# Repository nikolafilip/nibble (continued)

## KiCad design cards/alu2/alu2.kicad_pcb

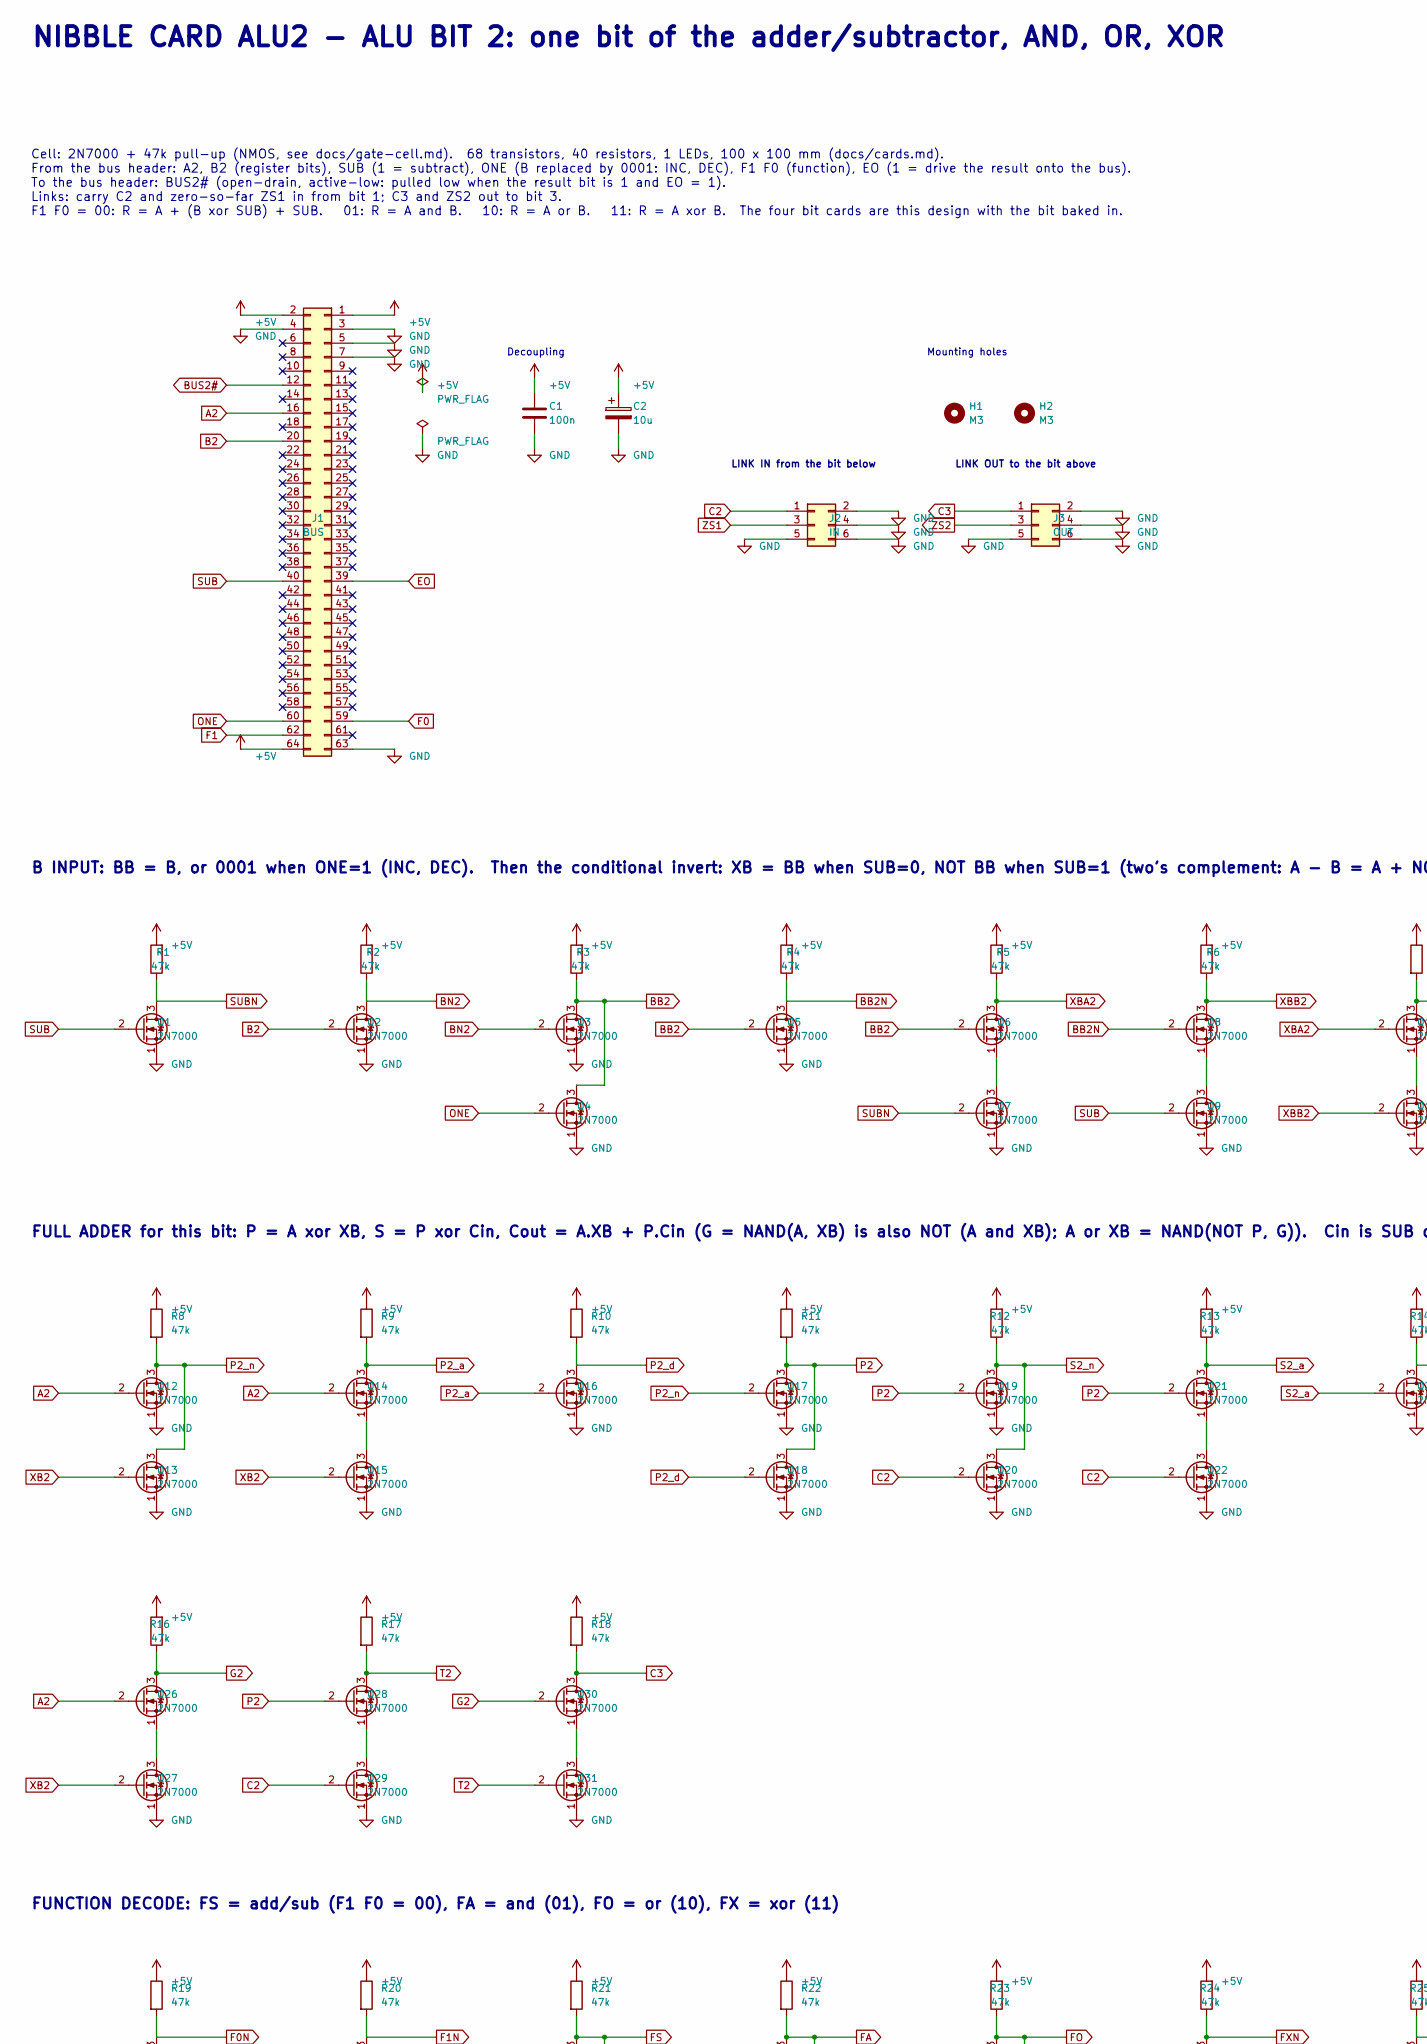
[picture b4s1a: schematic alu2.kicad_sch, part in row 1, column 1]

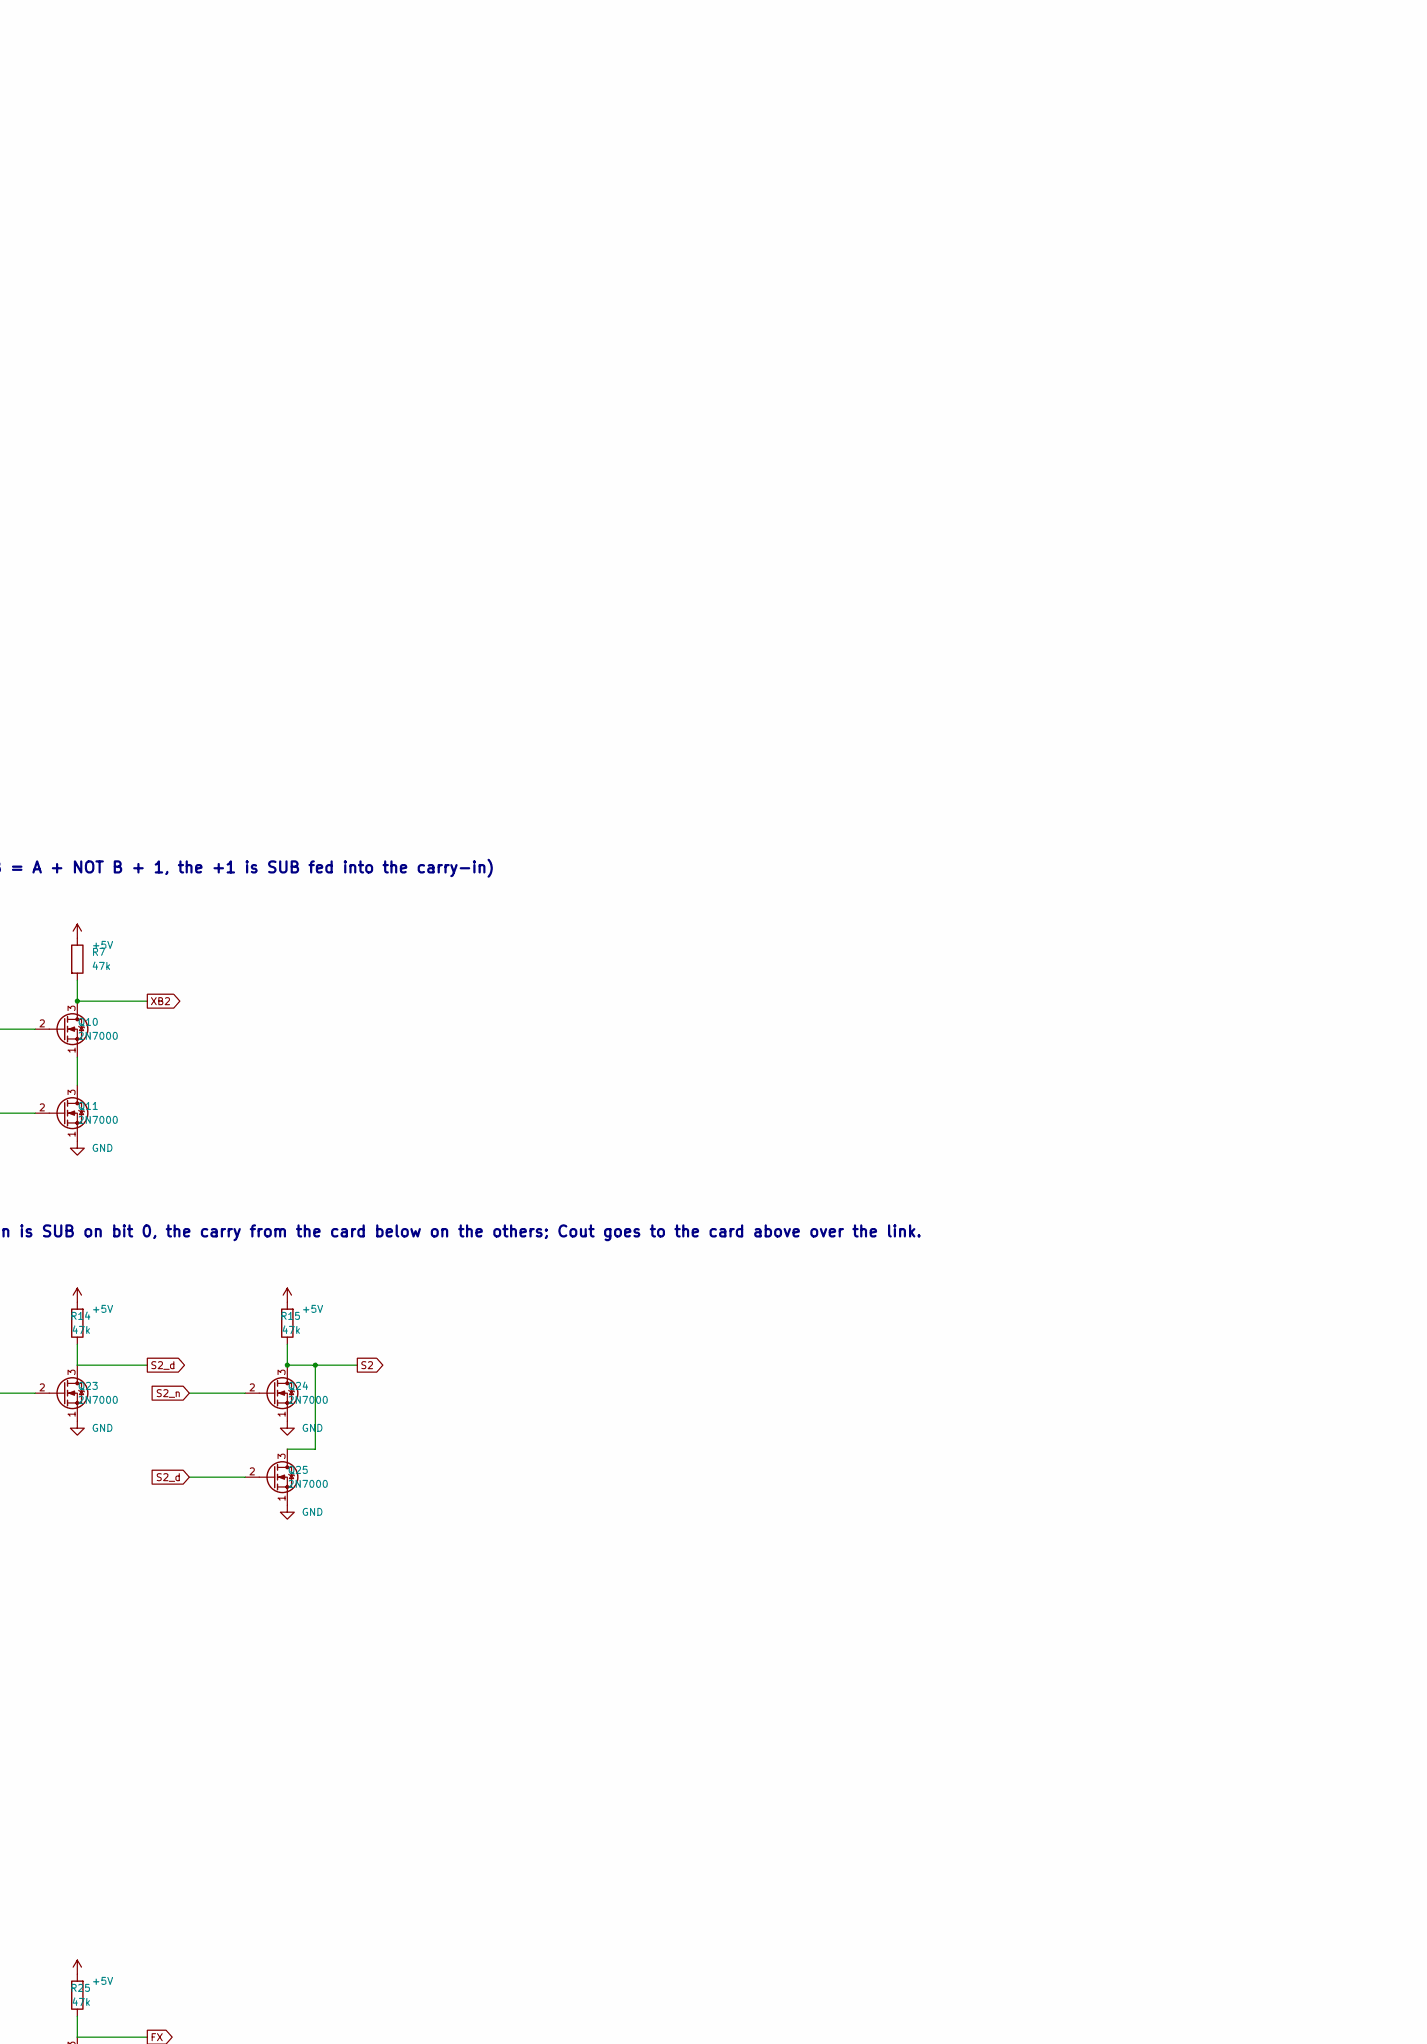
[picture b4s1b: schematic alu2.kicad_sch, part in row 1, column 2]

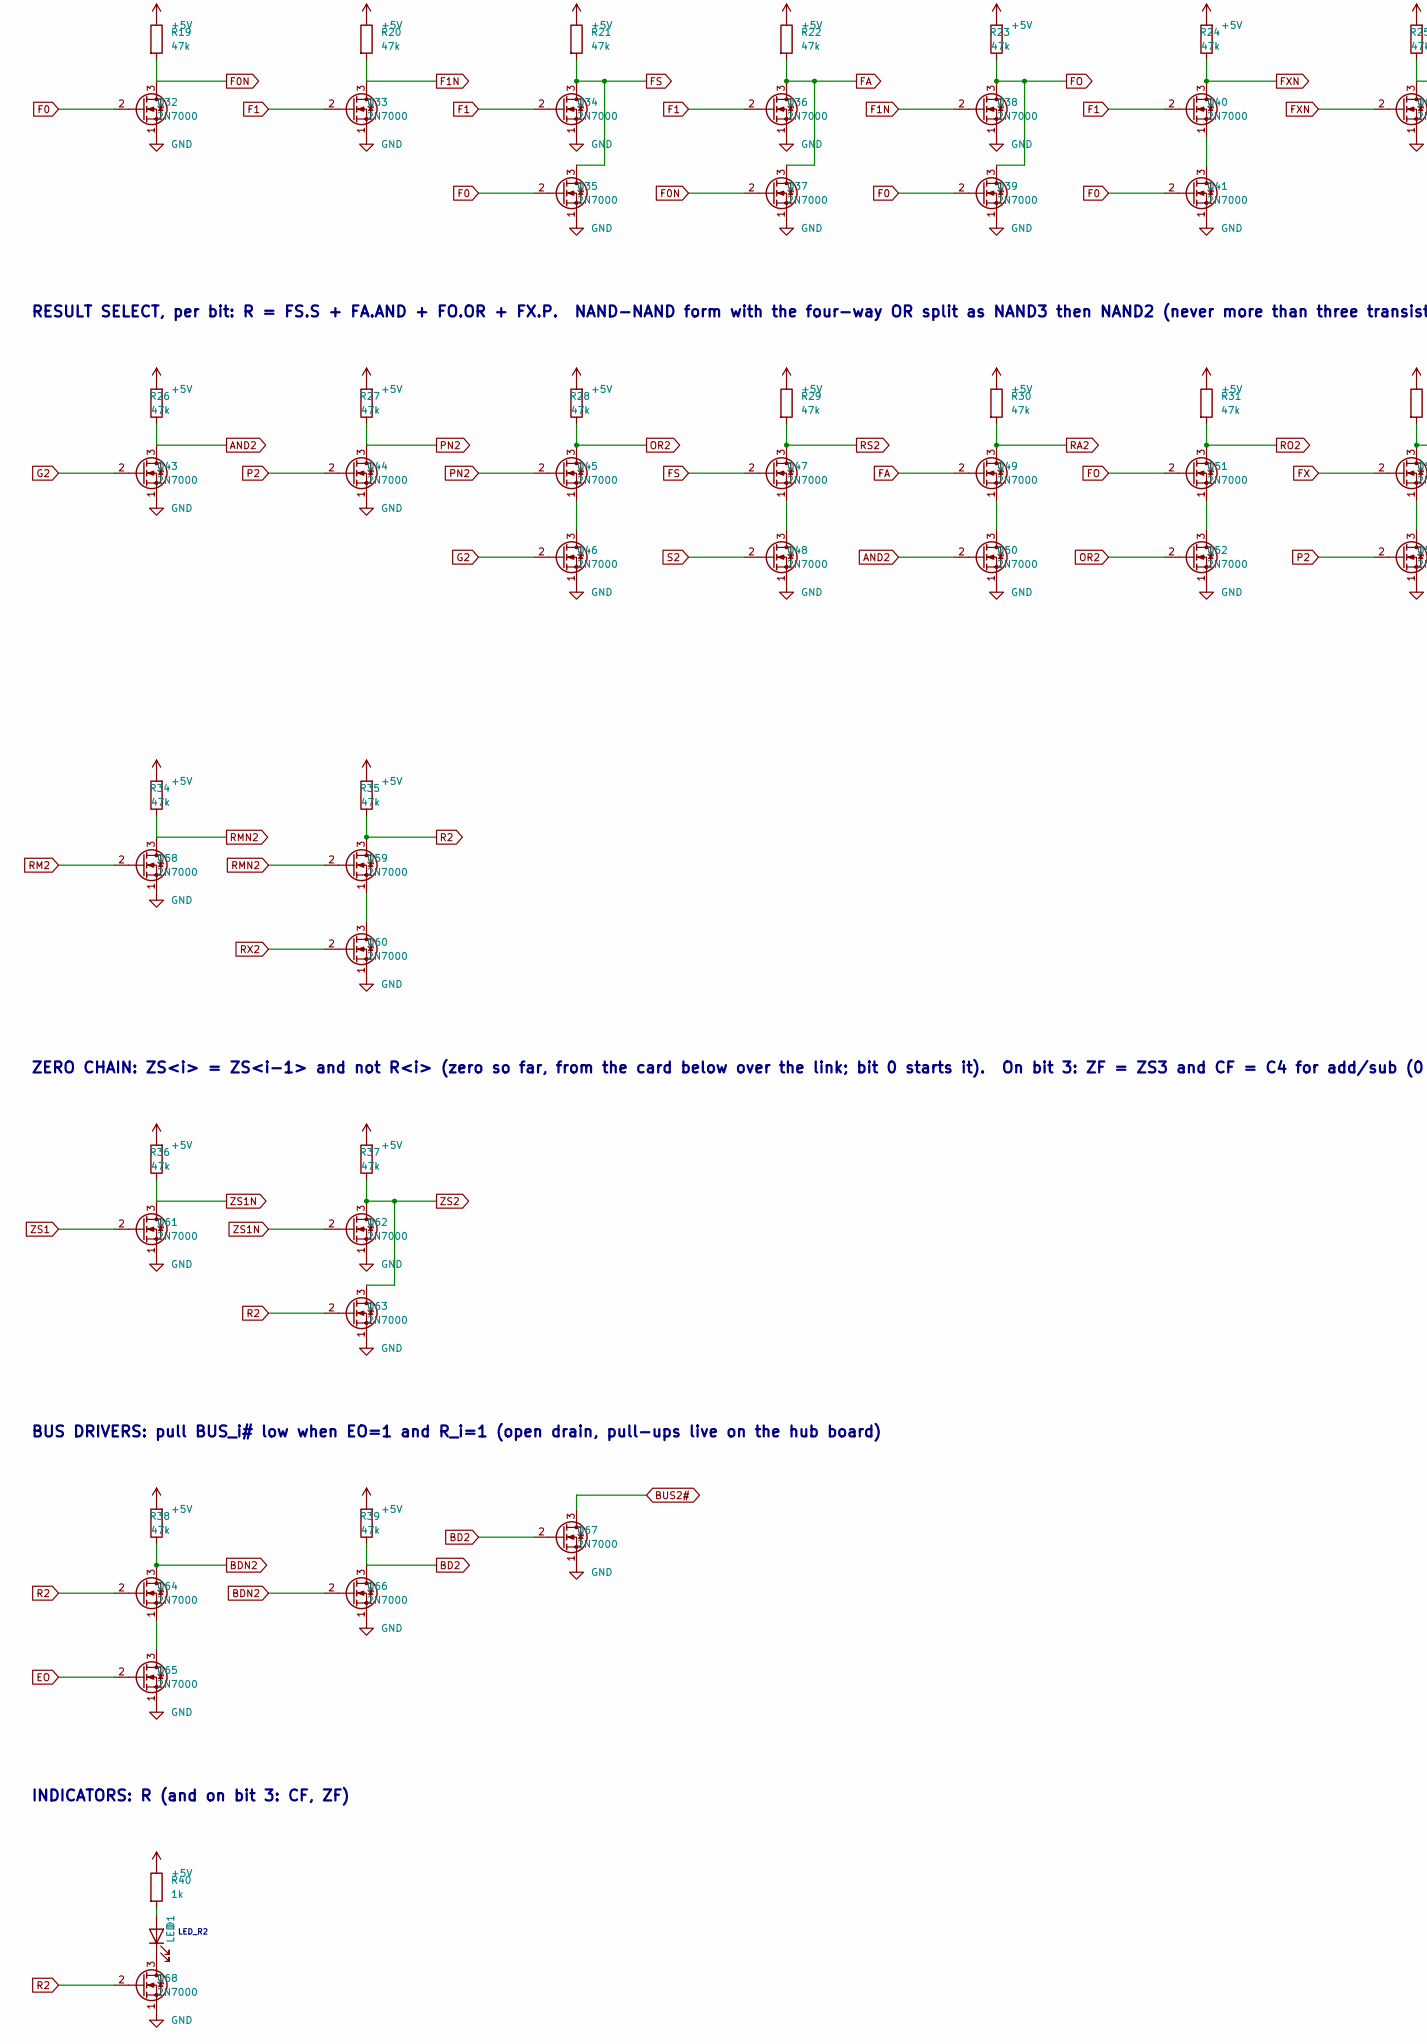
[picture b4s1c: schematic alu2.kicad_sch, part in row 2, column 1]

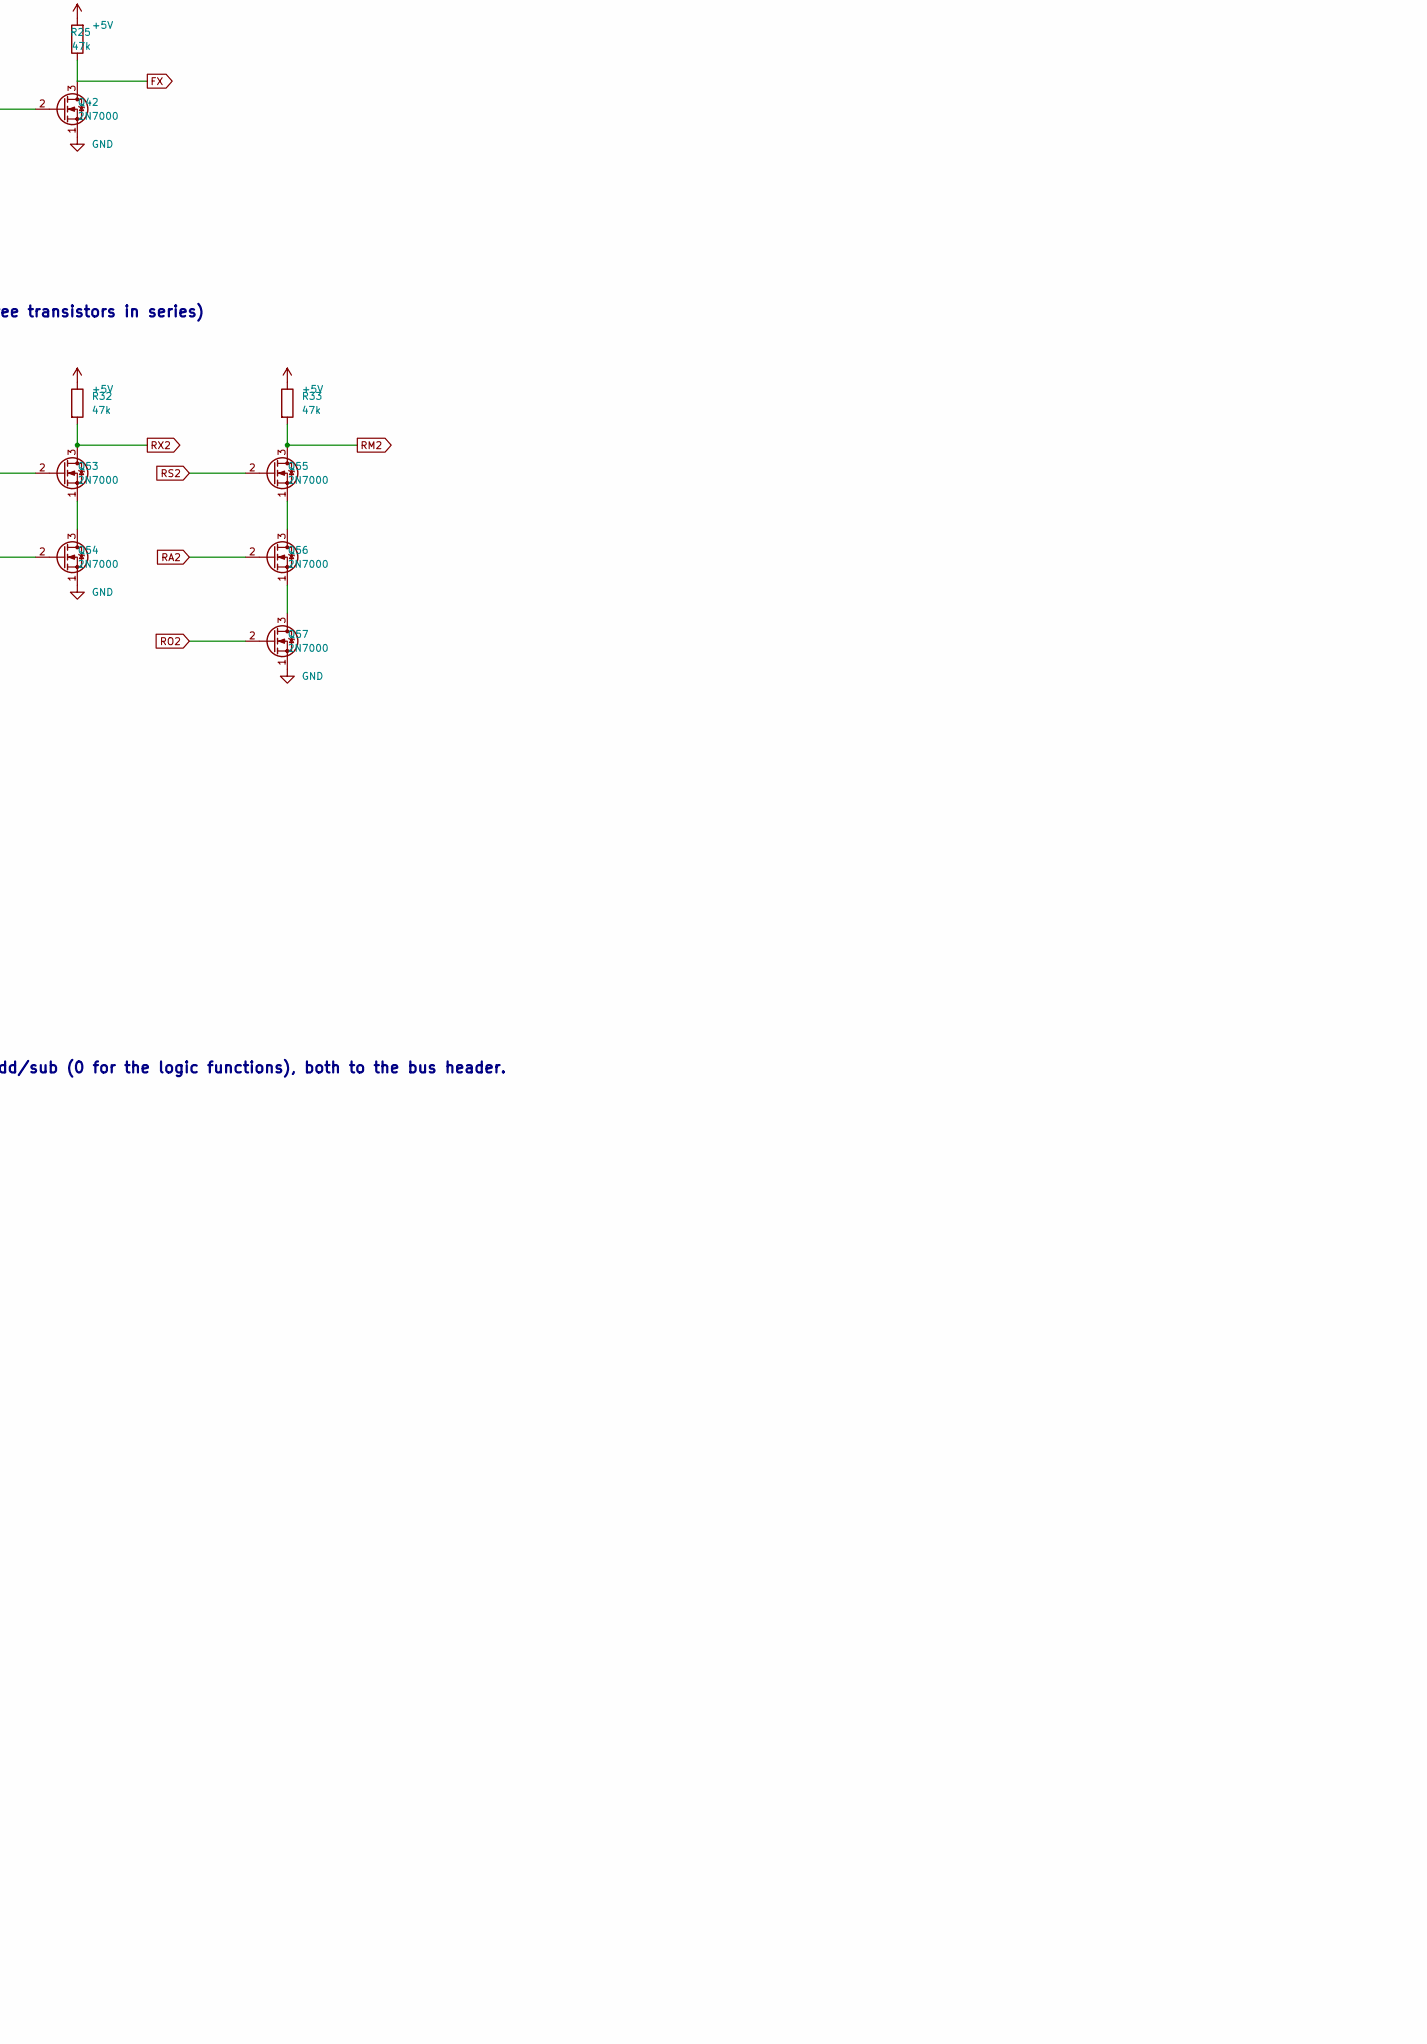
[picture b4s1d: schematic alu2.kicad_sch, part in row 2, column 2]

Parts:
C1: 100n; C_Disc_D5.0mm_W2.5mm_P2.50mm
C2: 10u; CP_Radial_D5.0mm_P2.00mm
D1: LED; LED_D3.0mm
H1, H2: M3; MountingHole_3.2mm_M3_Pad
J1: BUS; IDC-Header_2x32_P2.54mm_Vertical
J2: IN; IDC-Header_2x03_P2.54mm_Vertical
J3: OUT; IDC-Header_2x03_P2.54mm_Vertical
Q1, Q2, Q3, Q4, Q5, Q6, Q7, Q8, Q9, Q10, Q11, Q12, Q13, Q14, Q15, Q16, Q17, Q18, Q19, Q20, Q21, Q22, Q23, Q24, Q25, Q26, Q27, Q28, Q29, Q30, Q31, Q32, Q33, Q34, Q35, Q36, Q37, Q38, Q39, Q40, Q41, Q42, Q43, Q44, Q45, Q46, Q47, Q48, Q49, Q50, Q51, Q52, Q53, Q54, Q55, Q56, Q57, Q58, Q59, Q60, Q61, Q62, Q63, Q64, Q65, Q66, Q67, Q68: 2N7000; TO-92_Inline_Wide
R1, R2, R3, R4, R5, R6, R7, R8, R9, R10, R11, R12, R13, R14, R15, R16, R17, R18, R19, R20, R21, R22, R23, R24, R25, R26, R27, R28, R29, R30, R31, R32, R33, R34, R35, R36, R37, R38, R39: 47k; R_Axial_DIN0207_L6.3mm_D2.5mm_P5.08mm_Vertical
R40: 1k; R_Axial_DIN0207_L6.3mm_D2.5mm_P5.08mm_Vertical

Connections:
+5V: C1.1, C2.1, J1.1, J1.2, J1.64, R1.2, R2.2, R3.2, R4.2, R5.2, R6.2, R7.1, R8.1, R9.1, R10.1, R11.1, R12.2, R13.2, R14.2, R15.2, R16.2, R17.1, R18.1, R19.1, R20.1, R21.1, R22.1, R23.2, R24.2, R25.2, R26.2, R27.2, R28.2, R29.1, R30.1, R31.1, R32.1, R33.1, R34.2, R35.2, R36.2, R37.2, R38.2, R39.2, R40.1
A2: J1.16, Q12.2 (G), Q14.2 (G), Q26.2 (G)
AND2: Q43.3 (D), Q50.2 (G), R26.1
B2: J1.20, Q2.2 (G)
BB2: Q3.3 (D), Q4.3 (D), Q5.2 (G), Q6.2 (G), R3.1
BB2N: Q5.3 (D), Q8.2 (G), R4.1
BD2: Q66.3 (D), Q67.2 (G), R39.1
BDN2: Q64.3 (D), Q66.2 (G), R38.1
BN2: Q2.3 (D), Q3.2 (G), R2.1
BUS2#: J1.12, Q67.3 (D)
C2: J2.1, Q20.2 (G), Q22.2 (G), Q29.2 (G)
C3: J3.1, Q30.3 (D), R18.2
EO: J1.39, Q65.2 (G)
F0: J1.59, Q32.2 (G), Q35.2 (G), Q39.2 (G), Q41.2 (G)
F0N: Q32.3 (D), Q37.2 (G), R19.2
F1: J1.62, Q33.2 (G), Q34.2 (G), Q36.2 (G), Q40.2 (G)
F1N: Q33.3 (D), Q38.2 (G), R20.2
FA: Q36.3 (D), Q37.3 (D), Q49.2 (G), R22.2
FO: Q38.3 (D), Q39.3 (D), Q51.2 (G), R23.1
FS: Q34.3 (D), Q35.3 (D), Q47.2 (G), R21.2
FX: Q42.3 (D), Q53.2 (G), R25.1
FXN: Q40.3 (D), Q42.2 (G), R24.1
G2: Q26.3 (D), Q30.2 (G), Q43.2 (G), Q46.2 (G), R16.1
GND: C1.2, C2.2, J1.3, J1.4, J1.5, J1.7, J1.63, J2.2, J2.4, J2.5, J2.6, J3.2, J3.4, J3.5, J3.6, Q1.1 (S), Q2.1 (S), Q3.1 (S), Q4.1 (S), Q5.1 (S), Q7.1 (S), Q9.1 (S), Q11.1 (S), Q12.1 (S), Q13.1 (S), Q15.1 (S), Q16.1 (S), Q17.1 (S), Q18.1 (S), Q19.1 (S), Q20.1 (S), Q22.1 (S), Q23.1 (S), Q24.1 (S), Q25.1 (S), Q27.1 (S), Q29.1 (S), Q31.1 (S), Q32.1 (S), Q33.1 (S), Q34.1 (S), Q35.1 (S), Q36.1 (S), Q37.1 (S), Q38.1 (S), Q39.1 (S), Q41.1 (S), Q42.1 (S), Q43.1 (S), Q44.1 (S), Q46.1 (S), Q48.1 (S), Q50.1 (S), Q52.1 (S), Q54.1 (S), Q57.1 (S), Q58.1 (S), Q60.1 (S), Q61.1 (S), Q62.1 (S), Q63.1 (S), Q65.1 (S), Q66.1 (S), Q67.1 (S), Q68.1 (S)
unnamed: D1.2 (A), R40.2
unnamed: D1.1 (K), Q68.3 (D)
unnamed: Q6.1 (S), Q7.3 (D)
unnamed: Q8.1 (S), Q9.3 (D)
unnamed: Q10.1 (S), Q11.3 (D)
unnamed: Q14.1 (S), Q15.3 (D)
unnamed: Q21.1 (S), Q22.3 (D)
unnamed: Q26.1 (S), Q27.3 (D)
unnamed: Q28.1 (S), Q29.3 (D)
unnamed: Q30.1 (S), Q31.3 (D)
unnamed: Q40.1 (S), Q41.3 (D)
unnamed: Q45.1 (S), Q46.3 (D)
unnamed: Q47.1 (S), Q48.3 (D)
unnamed: Q49.1 (S), Q50.3 (D)
unnamed: Q51.1 (S), Q52.3 (D)
unnamed: Q53.1 (S), Q54.3 (D)
unnamed: Q55.1 (S), Q56.3 (D)
unnamed: Q56.1 (S), Q57.3 (D)
unnamed: Q59.1 (S), Q60.3 (D)
unnamed: Q64.1 (S), Q65.3 (D)
ONE: J1.60, Q4.2 (G)
OR2: Q45.3 (D), Q52.2 (G), R28.1
P2: Q17.3 (D), Q18.3 (D), Q19.2 (G), Q21.2 (G), Q28.2 (G), Q44.2 (G), Q54.2 (G), R11.2
P2_a: Q14.3 (D), Q16.2 (G), R9.2
P2_d: Q16.3 (D), Q18.2 (G), R10.2
P2_n: Q12.3 (D), Q13.3 (D), Q17.2 (G), R8.2
PN2: Q44.3 (D), Q45.2 (G), R27.1
R2: Q59.3 (D), Q63.2 (G), Q64.2 (G), Q68.2 (G), R35.1
RA2: Q49.3 (D), Q56.2 (G), R30.2
RM2: Q55.3 (D), Q58.2 (G), R33.2
RMN2: Q58.3 (D), Q59.2 (G), R34.1
RO2: Q51.3 (D), Q57.2 (G), R31.2
RS2: Q47.3 (D), Q55.2 (G), R29.2
RX2: Q53.3 (D), Q60.2 (G), R32.2
S2: Q24.3 (D), Q25.3 (D), Q48.2 (G), R15.1
S2_a: Q21.3 (D), Q23.2 (G), R13.1
S2_d: Q23.3 (D), Q25.2 (G), R14.1
S2_n: Q19.3 (D), Q20.3 (D), Q24.2 (G), R12.1
SUB: J1.40, Q1.2 (G), Q9.2 (G)
SUBN: Q1.3 (D), Q7.2 (G), R1.1
T2: Q28.3 (D), Q31.2 (G), R17.2
XB2: Q10.3 (D), Q13.2 (G), Q15.2 (G), Q27.2 (G), R7.2
XBA2: Q6.3 (D), Q10.2 (G), R5.1
XBB2: Q8.3 (D), Q11.2 (G), R6.1
ZS1: J2.3, Q61.2 (G)
ZS1N: Q61.3 (D), Q62.2 (G), R36.1
ZS2: J3.3, Q62.3 (D), Q63.3 (D), R37.1

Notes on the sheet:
NIBBLE CARD ALU2 - ALU BIT 2: one bit of the adder/subtractor, AND, OR, XOR
Cell: 2N7000 + 47k pull-up (NMOS, see docs/gate-cell.md). 68 transistors, 40 resistors, 1 LEDs, 100 x 100 mm (docs/cards.md). From the bus header: A2, B2 (register bits), SUB (1 = subtract), ONE (B replaced by 0001: INC, DEC), F1 F0 (function), EO (1 = drive the result onto the bus). To the bus hea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
B INPUT: BB = B, or 0001 when ONE=1 (INC, DEC). Then the conditional invert: XB = BB when SUB=0, NOT BB when SUB=1 (two's complement: A - B = A + NOT B + 1, the +1 is SUB fed into the carry-in)
FULL ADDER for this bit: P = A xor XB, S = P xor Cin, Cout = A.XB + P.Cin (G = NAND(A, XB) is also NOT (A and XB); A or XB = NAND(NOT P, G)). Cin is SUB on bit 0, the carry from the card below on the others; Cout goes to the card above over the link.
FUNCTION DECODE: FS = add/sub (F1 F0 = 00), FA = and (01), FO = or (10), FX = xor (11)
RESULT SELECT, per bit: R = FS.S + FA.AND + FO.OR + FX.P. NAND-NAND form with the four-way OR split as NAND3 then NAND2 (never more than three transistors in series)
ZERO CHAIN: ZS<i> = ZS<i-1> and not R<i> (zero so far, from the card below over the link; bit 0 starts it). On bit 3: ZF = ZS3 and CF = C4 for add/sub (0 for the logic functions), both to the bus header.
BUS DRIVERS: pull BUS_i# low when EO=1 and R_i=1 (open drain, pull-ups live on the hub board)
INDICATORS: R (and on bit 3: CF, ZF)
LED_R2
Decoupling
Mounting holes
LINK IN from the bit below
LINK OUT to the bit above

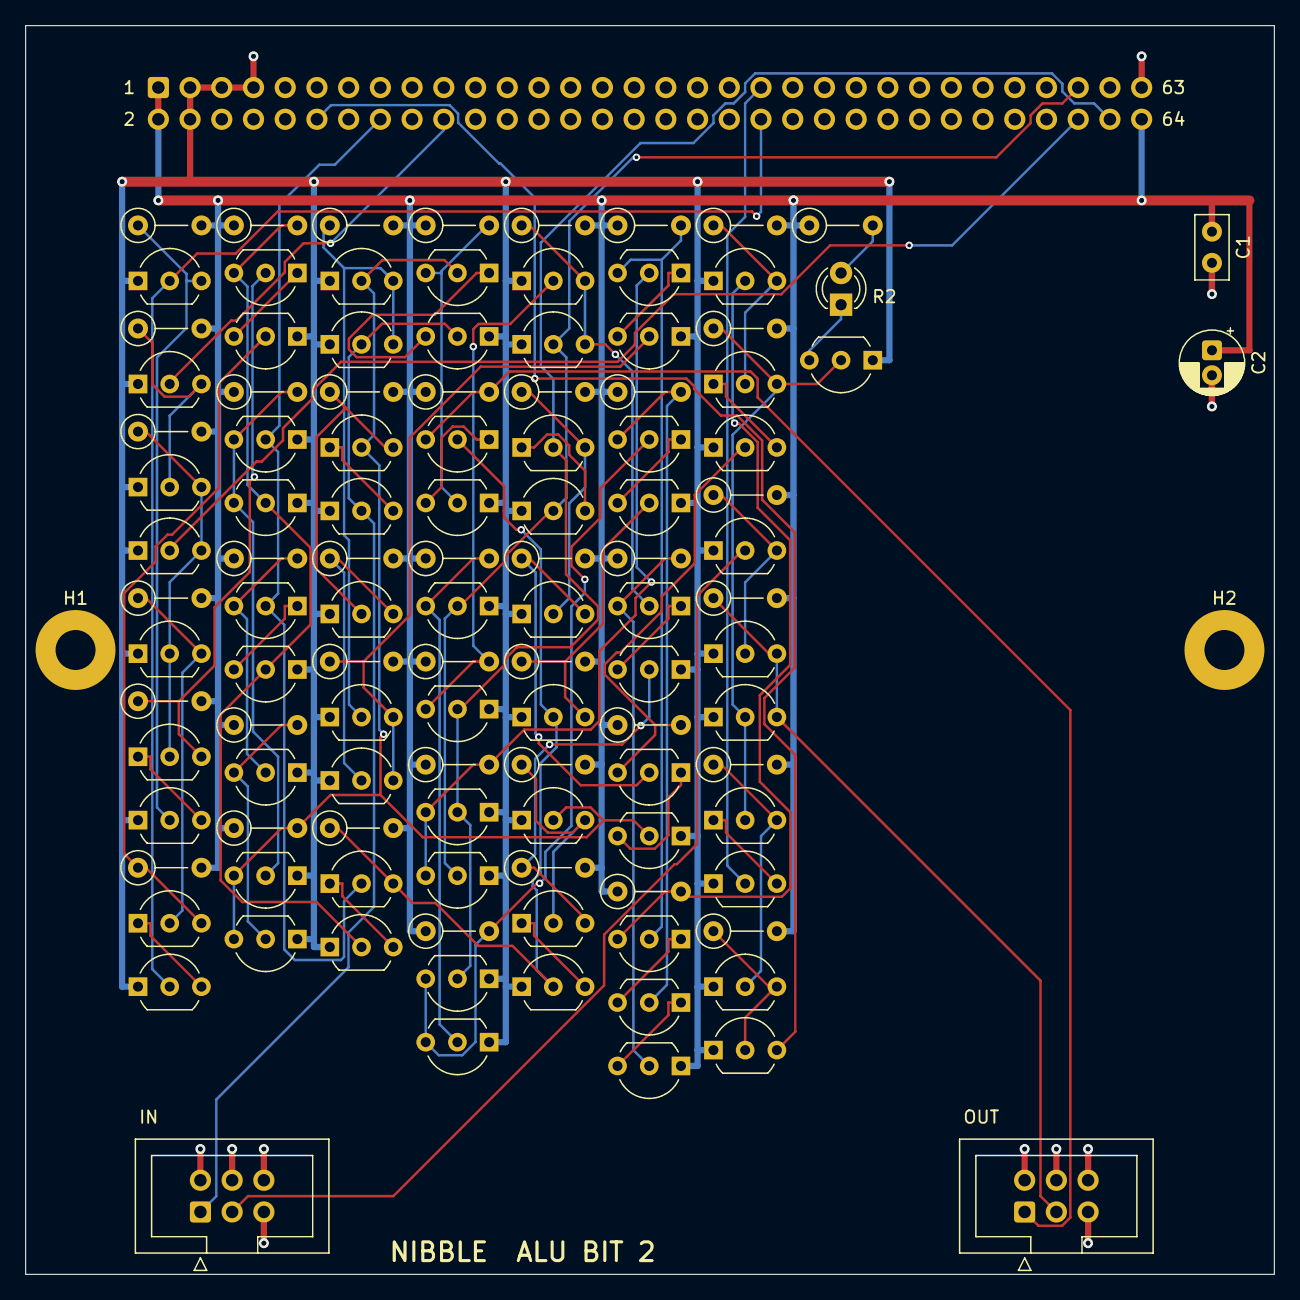
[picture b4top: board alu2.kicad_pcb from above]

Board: 2 copper layers, 100.0 x 100.0 mm, 116 parts (1 on the bottom side), 71 nets.

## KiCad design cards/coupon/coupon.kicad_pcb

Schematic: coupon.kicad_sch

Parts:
C1: 100n; C_Disc_D5.0mm_W2.5mm_P2.50mm
C2: 10u; CP_Radial_D5.0mm_P2.00mm
C3: 47n; C_Disc_D5.0mm_W2.5mm_P2.50mm
D1: LED; LED_D3.0mm
D2, D3: 1N4148; D_DO-35_SOD27_P7.62mm_Horizontal
H1, H2: M3; MountingHole_3.2mm_M3_Pad
J1: IN N1 N2 N3 RST GND; PinHeader_1x06_P2.54mm_Vertical
J2: +5V GND; PinHeader_1x02_P2.54mm_Vertical
J3: BUS; IDC-Header_2x32_P2.54mm_Vertical
Q1, Q2, Q3, Q4, Q5, Q6, Q7, Q8, Q9, Q10, Q11, Q12, Q13, Q14, Q15, Q16, Q17, Q18, Q19, Q20, Q21, Q22, Q23, Q24, Q25, Q26, Q27, Q28, Q29, Q30, Q31, Q32, Q33, Q34, Q35, Q36, Q37, Q38, Q39, Q40, Q41, Q42, Q43, Q44, Q45, Q46, Q47, Q48, Q49, Q50, Q51, Q52, Q53, Q54, Q55, Q56, Q57: 2N7000; TO-92_Inline_Wide
R1, R48, R52: 10k; R_Axial_DIN0207_L6.3mm_D2.5mm_P5.08mm_Vertical
R2, R3, R4, R5, R6, R7, R8, R9, R10, R11, R12, R13, R14, R15, R16, R17, R18, R19, R20, R21, R23, R24, R25, R26, R27, R28, R29, R30, R31, R32, R33, R34, R35, R36, R37, R47: 47k; R_Axial_DIN0207_L6.3mm_D2.5mm_P5.08mm_Vertical
R22, R39: 4.7k; R_Axial_DIN0207_L6.3mm_D2.5mm_P5.08mm_Vertical
R38, R41, R49: 1k; R_Axial_DIN0207_L6.3mm_D2.5mm_P5.08mm_Vertical
R40: 3.3k; R_Axial_DIN0207_L6.3mm_D2.5mm_P5.08mm_Vertical
R42, R43, R44, R45, R46: 1Meg; R_Axial_DIN0207_L6.3mm_D2.5mm_P5.08mm_Vertical
R50: 100k; R_Axial_DIN0207_L6.3mm_D2.5mm_P5.08mm_Vertical
R51: 100; R_Axial_DIN0207_L6.3mm_D2.5mm_P5.08mm_Vertical
R53: 220k; R_Axial_DIN0207_L6.3mm_D2.5mm_P5.08mm_Vertical
TP1: TP_RING; TestPoint_Loop_D2.50mm_Drill1.0mm
TP2: RING0; TestPoint_Loop_D2.50mm_Drill1.0mm
TP3: TP_FO1; TestPoint_Loop_D2.50mm_Drill1.0mm
TP4: TP_FO10; TestPoint_Loop_D2.50mm_Drill1.0mm
TP5: TP_NAND; TestPoint_Loop_D2.50mm_Drill1.0mm
TP6: TP_NOR; TestPoint_Loop_D2.50mm_Drill1.0mm
TP7: TP_BUS; TestPoint_Loop_D2.50mm_Drill1.0mm
TP8: TP_VTO; TestPoint_Loop_D2.50mm_Drill1.0mm
TP9: X; TestPoint_Loop_D2.50mm_Drill1.0mm
TP10: TP_OSC; TestPoint_Loop_D2.50mm_Drill1.0mm
TP11: TP_Q; TestPoint_Loop_D2.50mm_Drill1.0mm
TP12: TP_DRV; TestPoint_Loop_D2.50mm_Drill1.0mm
TP13: TP_ROM; TestPoint_Loop_D2.50mm_Drill1.0mm
TP14: GND; TestPoint_Loop_D2.50mm_Drill1.0mm
TP15: +5V; TestPoint_Loop_D2.50mm_Drill1.0mm

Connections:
+5V: C1.1, C2.1, J2.1, J3.1, J3.2, J3.64, R1.1, R2.2, R3.1, R4.2, R5.1, R6.2, R7.1, R8.2, R9.1, R10.2, R11.1, R12.2, R13.1, R14.2, R15.1, R16.2, R17.1, R18.2, R19.1, R20.2, R21.1, R22.1, R23.2, R24.1, R25.2, R26.1, R27.2, R28.1, R29.2, R30.1, R31.2, R32.2, R33.1, R34.1, R35.2, R36.2, R37.1, R38.1, R39.2, R40.1, R41.1, R47.1, R48.1, TP15.1
DRVN: Q52.3 (D), R38.2, R51.1
GND: C1.2, C2.2, C3.2, J1.6, J2.2, J3.3, J3.4, J3.5, J3.7, J3.63, Q1.1 (S), Q2.1 (S), Q3.1 (S), Q4.1 (S), Q5.1 (S), Q6.1 (S), Q7.1 (S), Q8.1 (S), Q9.1 (S), Q10.1 (S), Q11.1 (S), Q12.1 (S), Q13.1 (S), Q14.1 (S), Q15.1 (S), Q16.1 (S), Q17.1 (S), Q18.1 (S), Q21.1 (S), Q22.1 (S), Q23.1 (S), Q24.1 (S), Q25.1 (S), Q26.1 (S), Q27.1 (S), Q28.1 (S), Q29.1 (S), Q30.1 (S), Q31.1 (S), Q33.1 (S), Q35.1 (S), Q37.1 (S), Q40.1 (S), Q41.1 (S), Q43.1 (S), Q45.1 (S), Q47.1 (S), Q50.1 (S), Q51.1 (S), Q52.1 (S), Q53.1 (S), Q54.1 (S), Q55.1 (S), R42.1, R43.2, R44.1, R45.2, R46.1, R49.2, R52.2, R53.2, TP14.1
IN: J1.1, Q7.2 (G), Q25.2 (G), Q54.2 (G), Q55.2 (G), R42.2
LOAD0: Q9.3 (D), R10.1
LOAD1: Q10.3 (D), R11.2
LOAD2: Q11.3 (D), R12.1
LOAD3: Q12.3 (D), R13.2
LOAD4: Q13.3 (D), R14.1
LOAD5: Q14.3 (D), R15.2
LOAD6: Q15.3 (D), R16.1
LOAD7: Q16.3 (D), R17.2
LOAD8: Q17.3 (D), R18.1
LOAD9: Q18.3 (D), R19.2
N1: J1.2, Q19.2 (G), Q22.2 (G), R43.1
N2: J1.3, Q20.2 (G), Q23.2 (G), R44.2
N3: J1.4, Q21.2 (G), Q24.2 (G), R45.1
unnamed: D1.2 (A), R41.2
unnamed: D1.1 (K), Q55.3 (D)
unnamed: D2.2 (A), R51.2
unnamed: Q19.1 (S), Q20.3 (D)
unnamed: Q20.1 (S), Q21.3 (D)
unnamed: Q32.1 (S), Q33.3 (D)
unnamed: Q34.1 (S), Q35.3 (D)
unnamed: Q36.1 (S), Q37.3 (D)
unnamed: Q38.1 (S), Q39.3 (D)
unnamed: Q39.1 (S), Q40.3 (D)
unnamed: Q42.1 (S), Q43.3 (D)
unnamed: Q44.1 (S), Q45.3 (D)
unnamed: Q46.1 (S), Q47.3 (D)
unnamed: Q48.1 (S), Q49.3 (D)
unnamed: Q49.1 (S), Q50.3 (D)
unnamed: Q56.3 (D), Q57.2 (G), R47.2
QN: Q31.2 (G), Q32.2 (G), Q51.3 (D), R37.2
RING0: Q1.2 (G), Q5.3 (D), Q6.2 (G), R6.1, TP2.1
RING1: Q1.3 (D), Q2.2 (G), R2.1
RING2: Q2.3 (D), Q3.2 (G), R3.2
RING3: Q3.3 (D), Q4.2 (G), R4.1
RING4: Q4.3 (D), Q5.2 (G), R5.2
ROW: D3.2 (A), Q54.3 (D), R40.2
RST: J1.5, Q28.2 (G), R46.2
RSTN: Q28.3 (D), Q40.2 (G), Q50.2 (G), R24.2
SA: Q26.3 (D), Q27.2 (G), R22.2, R50.1
TP_BUS: Q25.3 (D), R1.2, TP7.1
TP_DRV: D2.1 (K), R52.1, TP12.1
TP_FO1: Q7.3 (D), Q8.2 (G), R8.1, TP3.1
TP_FO10: Q8.3 (D), Q9.2 (G), Q10.2 (G), Q11.2 (G), Q12.2 (G), Q13.2 (G), Q14.2 (G), Q15.2 (G), Q16.2 (G), Q17.2 (G), Q18.2 (G), R9.2, TP4.1
TP_NAND: Q19.3 (D), R20.1, TP5.1
TP_NOR: Q22.3 (D), Q23.3 (D), Q24.3 (D), R21.2, TP6.1
TP_OSC: Q27.3 (D), Q29.2 (G), Q52.2 (G), R23.1, TP10.1
TP_Q: Q46.3 (D), Q48.2 (G), Q51.2 (G), R35.1, TP11.1
TP_Q_ckb: Q30.3 (D), Q43.2 (G), Q44.2 (G), R26.2
TP_Q_ckn: Q29.3 (D), Q30.2 (G), Q33.2 (G), Q34.2 (G), R25.1
TP_Q_dn: Q31.3 (D), Q35.2 (G), R27.1
TP_Q_m1: Q32.3 (D), Q36.2 (G), R28.2
TP_Q_m2: Q34.3 (D), Q39.2 (G), R29.1
TP_Q_mq: Q36.3 (D), Q38.2 (G), Q41.2 (G), Q42.2 (G), R30.2
TP_Q_mqi: Q41.3 (D), Q45.2 (G), R32.1
TP_Q_mqn: Q37.2 (G), Q38.3 (D), R31.1
TP_Q_qn: Q47.2 (G), Q48.3 (D), R36.1
TP_Q_sa: Q42.3 (D), Q46.2 (G), R33.2
TP_Q_sb: Q44.3 (D), Q49.2 (G), R34.2
TP_RING: Q6.3 (D), R7.2, TP1.1
TP_ROM: D3.1 (K), R53.1, TP13.1
TP_VTO: Q53.2 (G), Q53.3 (D), R39.1, TP8.1
VD2: Q26.2 (G), Q57.3 (D), R48.2
VS: Q56.1 (S), Q57.1 (S), R49.1
X: C3.1, Q56.2 (G), R50.2, TP9.1

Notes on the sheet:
NIBBLE CARD COUPON: every cell of the machine in copper, measured before any card is trusted
57 transistors, 100 x 100 mm (docs/cards.md). Power: 5 V on the 2-pin header from the bench supply (limit 300 mA), or the bus header (the hub; no other bus line is used). Drive IN, N1, N2, N3, RST from the 6-pin header (each has a 1Meg pull-down, so open = 0; RST open lets the flip-flop run). Measu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
Bench supply in, 5.0 V, current limit 300 mA
TEST LOOPS
hub pull-up
RING OSCILLATOR: 5 inverters in a loop, buffered to TP_RING. Period = 10 gate delays.
FAN-OUT: IN -> INV_A (drives 1 gate, TP_FO1) -> INV_B (drives 10 gates, TP_FO10). Compare rise times.
3-INPUT NAND (three in series, TP_NAND) and 3-INPUT NOR (three in parallel, TP_NOR) on N1..N3. Measure output low.
BUS DRIVER: open drain on IN, 10k pull-up as on the hub, TP_BUS.
OSCILLATOR BUFFERS (the clock card's): SA = NOT VD2 (VD2 is the Schmitt pair's output, drawn below) with a 4.7k pull-up drives 100k back to X; SB = NOT SA is the clock, TP_OSC.
TOGGLE FLIP-FLOP: the NAND master-slave D flip-flop (nmos.ff) with D = NOT Q, clocked by SB, reset by RSTN = NOT RST. TP_Q runs at half the oscillator rate while RST is low; RST high holds it at 0.
LINE DRIVER (D053): DRVN = NOT SB with a 1k pull-up, through 100 ohm and a diode (drawn below) into TP_DRV with a 10k pull-down. Clip 3.3 nF on TP_DRV: the CLK edge every card sees.
THRESHOLD: gate tied to drain, 4.7k pull-up. TP_VTO settles about 0.1 V above this transistor's threshold (0.6 mA).
PROGRAM ROW: ROW = NOT IN with a 3.3k pull-up, through a 1N4148 (drawn below) into TP_ROM with the hub's 220k pull-down. TP_ROM high = 5 V less a diode.
INDICATOR: LED on IN.
LED_IN
Decoupling
Mounting holes
SCHMITT TRIGGER (the clock card's, cards/clock): Q1 (gate X) and Q2 (gate = Q1's drain) share RS = 1k. Q2 on: source at 0.45 V (RD2 10k); Q1 on: source at 0.1 V (RD1 47k). VD2, Q2's drain, is the output: 0.5 V with X low, 5 V with X high.
TIMING: SA -> 100k -> X, 47n from X to GND: the clock card at its fastest setting (its pot at zero), about 500 Hz. X swings only between the two trip points, about half a volt around Vth.
LINE DRIVER (D053): DRVN (1k pull-up) through 100 ohm and a diode into TP_DRV with a 10k pull-down, as the clock card drives CLK and RST and the panel its buttons. Clip 3.3 nF from TP_DRV to GND: the ribbon and the cards' gates.
PROGRAM ROW: ROW (3.3k pull-up) through a 1N4148 into TP_ROM with the hub's 220k pull-down (D048): the M line's high is 5 V less a diode drop.

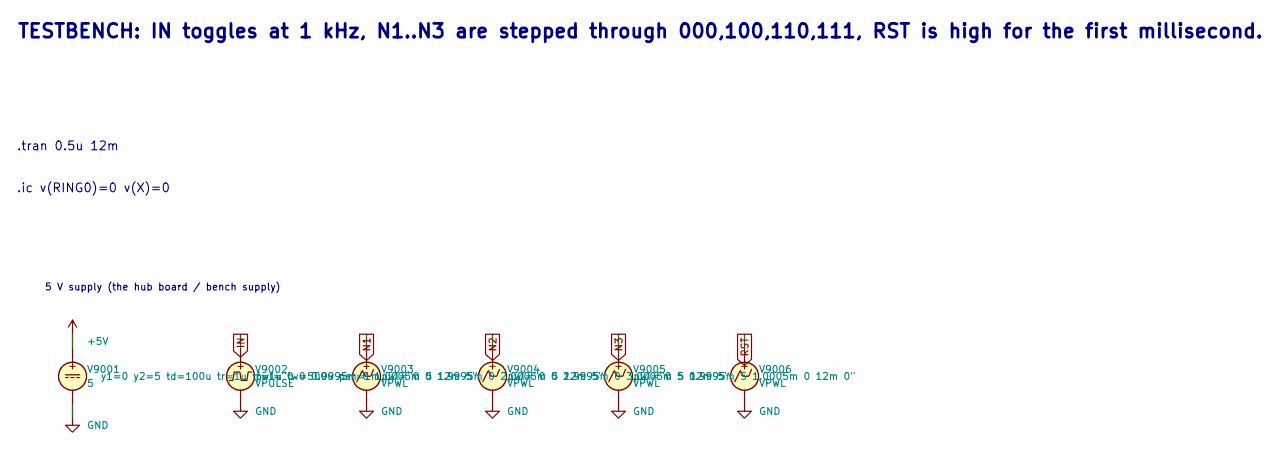
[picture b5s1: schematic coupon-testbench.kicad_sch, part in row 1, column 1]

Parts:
V9001: 5
V9002: VPULSE
V9003, V9004, V9005, V9006: VPWL

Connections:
unnamed: V9001.2, V9002.2, V9003.2, V9004.2, V9005.2, V9006.2

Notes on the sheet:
TESTBENCH: IN toggles at 1 kHz, N1..N3 are stepped through 000,100,110,111, RST is high for the first millisecond. Excluded from the board; sim/tb_coupon.py is the measured bench.
.tran 0.5u 12m
.ic v(RING0)=0 v(X)=0
5 V supply (the hub board / bench supply)
